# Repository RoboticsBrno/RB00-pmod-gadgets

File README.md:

# pmod-gadgets

Repozitář se všemi rozšířenímí pro desky nejen z [Robotického tábora]("https://robotickytabor.cz")

- [Jak přidat svůj projekt](PMOD.md)

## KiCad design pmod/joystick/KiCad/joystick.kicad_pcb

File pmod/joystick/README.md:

# Joystick PMOD

Tento modul umožňuje připojit joystick k vašemu systému PMOD. Poskytuje jednoduché rozhraní pro čtení polohy páčky a tlačítka.

[Manuál](manual.md){ .md-button .md-button--primary }

|  |  |
| --- | --- |

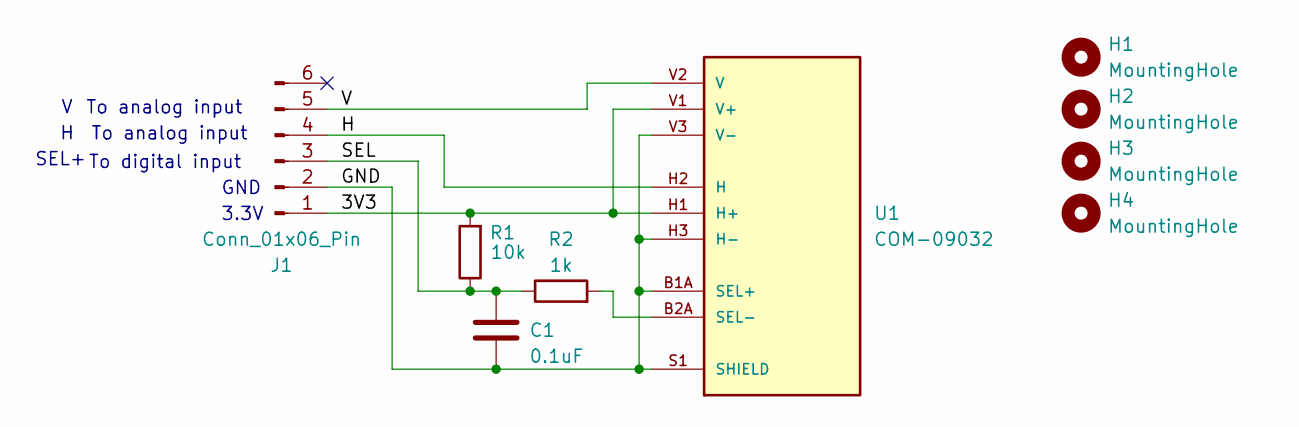
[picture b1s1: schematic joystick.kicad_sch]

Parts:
C1: 0.1uF; C_1206_3216Metric_Pad1.33x1.80mm_HandSolder
H1, H2, H3, H4: MountingHole; MountingHole_3.2mm_M3
J1: Conn_01x06_Pin; PinHeader_1x06_P2.54mm_Horizontal
R1: 10k; R_1206_3216Metric_Pad1.30x1.75mm_HandSolder
R2: 1k; R_1206_3216Metric_Pad1.30x1.75mm_HandSolder
U1: COM-09032; joystick; PARTREV N/A

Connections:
/3V3: J1.1, R1.2, U1.H1 (H+), U1.V1 (V+)
/GND: C1.2, J1.2, U1.B1A (SEL+), U1.H3 (H-), U1.S1 (SHIELD), U1.S2 (SHIELD), U1.S3 (SHIELD), U1.S4 (SHIELD), U1.V3 (V-)
/H: J1.4, U1.H2 (H)
/SEL: C1.1, J1.3, R1.1, R2.1
/V: J1.5, U1.V2 (V)
unnamed: R2.2, U1.B2A (SEL-)

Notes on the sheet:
3.3V
To digital input
To analog input
SEL+
GND

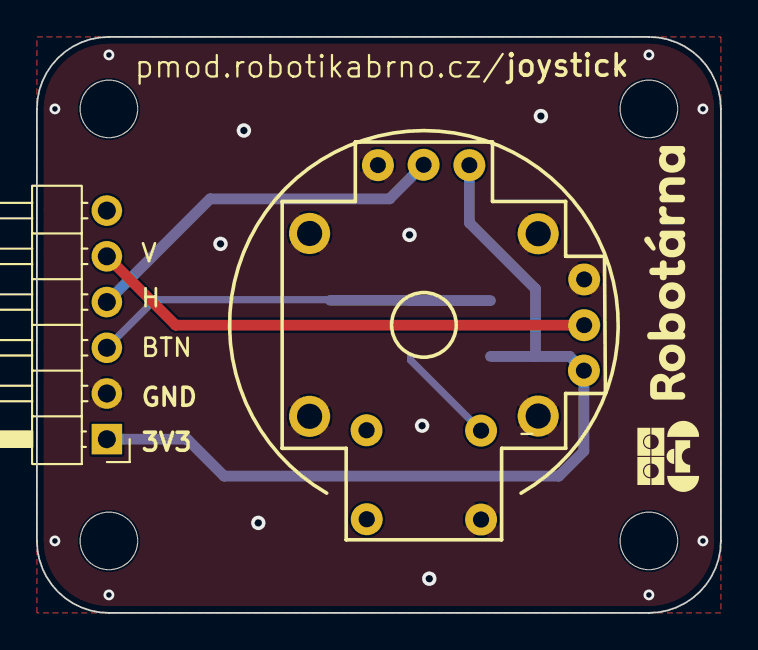
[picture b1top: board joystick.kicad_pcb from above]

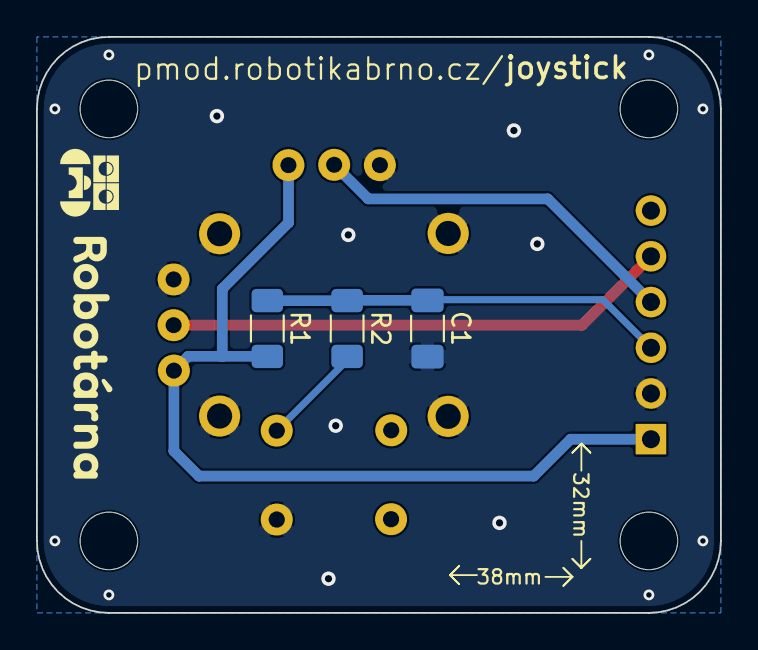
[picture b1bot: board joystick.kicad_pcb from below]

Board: 2 copper layers, 38.0 x 32.0 mm, 9 parts (3 on the bottom side), 6 nets.

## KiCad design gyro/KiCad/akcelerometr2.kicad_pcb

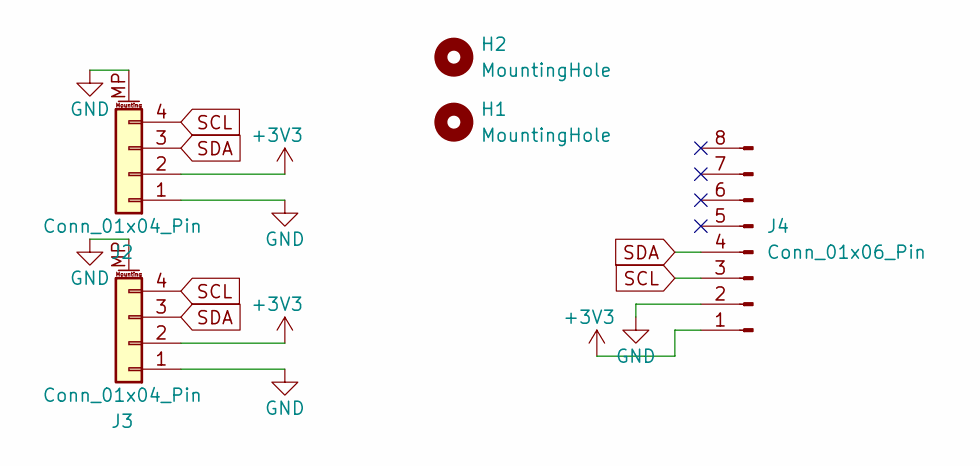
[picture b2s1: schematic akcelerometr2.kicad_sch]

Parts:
H1, H2: MountingHole; MountingHole_3.2mm_M3
J2, J3: Conn_01x04_Pin; JST_SH_SM04B-SRSS-TB_1x04-1MP_P1.00mm_Horizontal; LCSC C160404
J4: Conn_01x06_Pin; PinHeader_1x08_P2.54mm_Vertical

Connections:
+3V3: J2.2, J3.2, J4.1
GND: J2.1, J2.MP (MountPin), J3.1, J3.MP (MountPin), J4.2
SCL: J2.4, J3.4, J4.3
SDA: J2.3, J3.3, J4.4

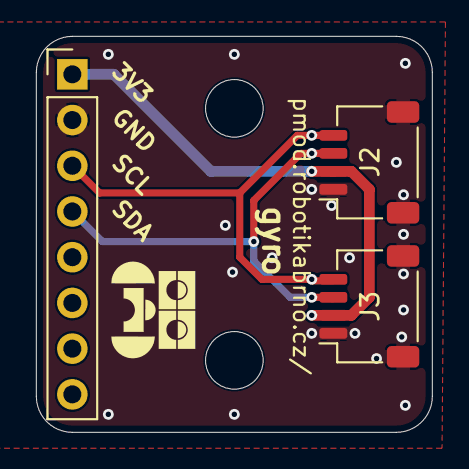
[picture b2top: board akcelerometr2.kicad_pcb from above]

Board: 2 copper layers, 22.0 x 22.0 mm, 5 parts (0 on the bottom side), 4 nets.

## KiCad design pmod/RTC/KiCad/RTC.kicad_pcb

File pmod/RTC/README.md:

# Připojovací modul pro RTC (reálný čas)

Tato deska slouží jako propojovací rozhraní pro snadnou integraci externího RTC modulu (modulu reálného času) do vašeho projektu.

[Manuál](manual.md){ .md-button .md-button--primary }

|  |  |
| --- | --- |

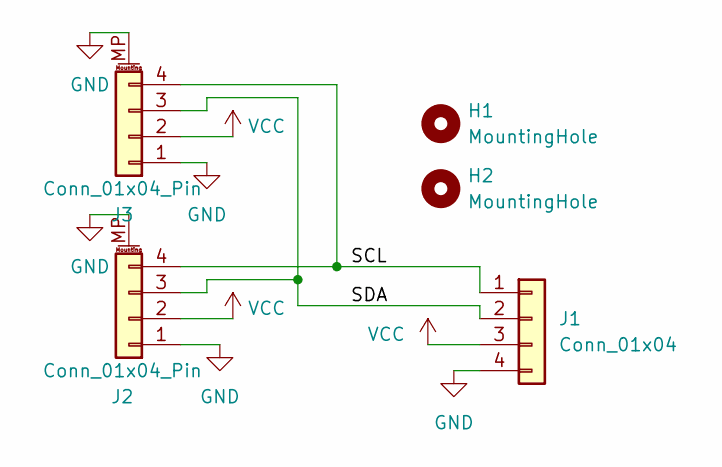
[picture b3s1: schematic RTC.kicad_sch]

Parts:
H1, H2: MountingHole; MountingHole_3.2mm_M3
J1: Conn_01x04; PinHeader_1x04_P2.54mm_Vertical
J2, J3: Conn_01x04_Pin; JST_SH_SM04B-SRSS-TB_1x04-1MP_P1.00mm_Horizontal; LCSC C160404

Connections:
/SCL: J1.1, J2.4, J3.4
/SDA: J1.2, J2.3, J3.3
GND: J1.4, J2.1, J2.MP (MountPin), J3.1, J3.MP (MountPin)
VCC: J1.3, J2.2, J3.2

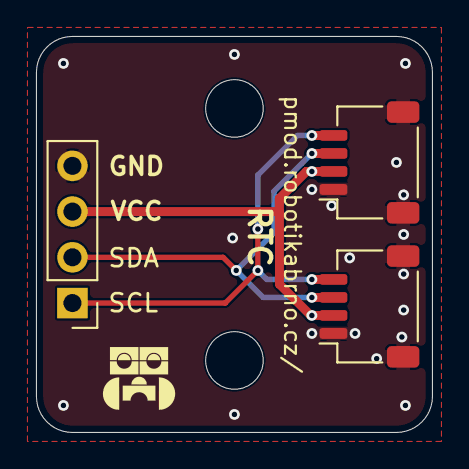
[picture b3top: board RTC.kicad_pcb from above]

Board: 2 copper layers, 22.0 x 22.0 mm, 5 parts (0 on the bottom side), 4 nets.

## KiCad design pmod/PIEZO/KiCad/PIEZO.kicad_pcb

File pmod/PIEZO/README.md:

# Piezoelektrický generátor zvuku

Tento modul slouží k vytváření zvuků pomocí piezoelektrického bzučáku.

[Manuál](manual.md){ .md-button .md-button--primary }

|  |  |
| --- | --- |

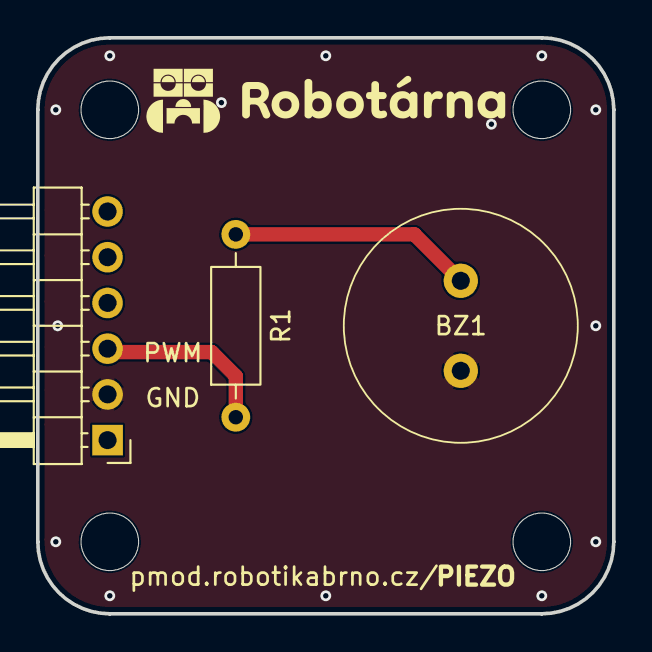
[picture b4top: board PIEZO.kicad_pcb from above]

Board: 2 copper layers, 32.0 x 32.0 mm, 3 parts (0 on the bottom side), 3 nets.

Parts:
BZ1: Buzzer; buzzer
J1: Conn_01x06_Pin; PinHeader_1x06_P2.54mm_Horizontal
R1: 330R; R_Axial_DIN0207_L6.3mm_D2.5mm_P10.16mm_Horizontal

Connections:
GND: BZ1.2 (-), J1.2
unnamed: BZ1.1 (+), R1.2
PWM: J1.3, R1.1

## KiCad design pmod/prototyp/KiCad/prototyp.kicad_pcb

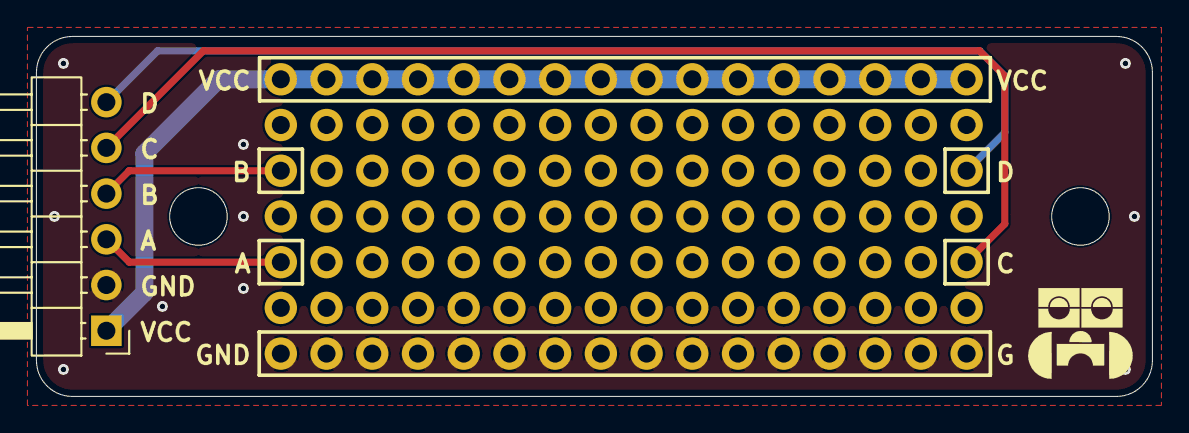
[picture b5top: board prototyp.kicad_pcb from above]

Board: 2 copper layers, 62.0 x 20.0 mm, 115 parts (0 on the bottom side), 6 nets.

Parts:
H1, H2, H3, H4, H5, H6, H7, H8, H9, H10, H11, H12, H13, H14, H15, H16, H17, H18, H19, H20, H21, H22, H23, H24, H25, H26, H27, H28, H29, H30, H31, H32, H33, H34, H35, H36, H37, H38, H39, H40, H41, H42, H43, H44, H45, H46, H47, H48, H49, H50, H51, H52, H53, H54, H55, H56, H57, H58, H59, H60, H61, H62, H63, H64, H65, H66, H67, H68, H69, H70, H71, H72, H73, H74, H75, H76, H77, H78, H79, H80, H81, H82, H83, H84, H85, H86, H87, H88, H89, H90, H91, H92, H93, H94, H95, H96, H97, H98, H99, H100, H101, H102, H103, H104, H105, H106, H107, H108, H109, H110, H111, H112: Hole
H113, H114: MountingHole; MountingHole_3.2mm_M3
J1: Conn_01x06_Pin; PinHeader_1x06_P2.54mm_Horizontal

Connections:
A: H33.1, J1.3
B: H65.1, J1.4
C: H48.1, J1.5
D: H80.1, J1.6
GND: H1.1, H2.1, H3.1, H4.1, H5.1, H6.1, H7.1, H8.1, H9.1, H10.1, H11.1, H12.1, H13.1, H14.1, H15.1, H16.1, J1.2
VCC: H97.1, H98.1, H99.1, H100.1, H101.1, H102.1, H103.1, H104.1, H105.1, H106.1, H107.1, H108.1, H109.1, H110.1, H111.1, H112.1, J1.1

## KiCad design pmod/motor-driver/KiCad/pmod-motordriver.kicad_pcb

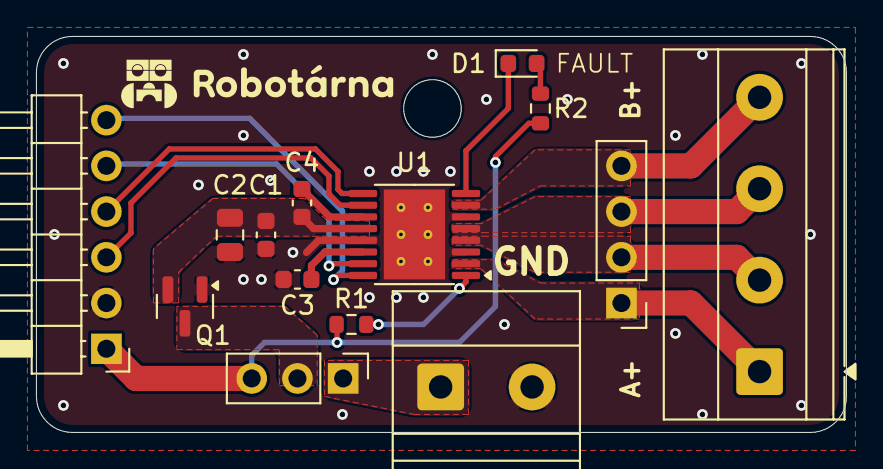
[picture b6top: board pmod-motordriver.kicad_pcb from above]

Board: 2 copper layers, 45.0 x 22.0 mm, 15 parts (0 on the bottom side), 18 nets.

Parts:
C1: 10u; C_0603_1608Metric
C2: 22u; C_0805_2012Metric
C3: 2.2u; C_0603_1608Metric
C4: 100n; C_0603_1608Metric
D1: LED; LED_0603_1608Metric
H1: MountingHole; MountingHole_3.2mm_M3
J1: Conn_01x06_Pin; PinHeader_1x06_P2.54mm_Horizontal
J2: Screw_Terminal_01x02; TerminalBlock_Phoenix_MKDS-1,5-2-5.08_1x02_P5.08mm_Horizont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
J4: Conn_01x04_Pin; PinHeader_1x04_P2.54mm_Vertical
J5: Screw_Terminal_01x04; TerminalBlock_Phoenix_MKDS-1,5-4-5.08_1x04_P5.08mm_Horizont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
JP1: Jumper_3_Bridged12; PinHeader_1x03_P2.54mm_Vertical
Q1: AO3401A; SOT-23
R1: 10k; R_0603_1608Metric
R2: 1k; R_0603_1608Metric
U1: DRV8833PWP; HTSSOP-16-1EP_4.4x5mm_P0.65mm_EP3.4x5mm_Mask2.46x2.31mm_The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

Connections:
+5V: J1.1, JP1.3 (B), R1.1, R2.1
/AOUT1: J4.1, J5.1, U1.2 (AOUT1)
/AOUT2: J4.2, J5.2, U1.4 (AOUT2)
/BOUT1: J4.4, J5.4, U1.7 (BOUT1)
/BOUT2: J4.3, J5.3, U1.5 (BOUT2)
AIN1: J1.6, U1.16 (AIN1)
AIN2: J1.5, U1.15 (AIN2)
BIN1: J1.4, U1.9 (BIN1)
BIN2: J1.3, U1.10 (BIN2)
GND: C1.2, C2.2, C3.2, J1.2, J2.2, Q1.1 (G), U1.3 (AISEN), U1.6 (BISEN), U1.13 (GND), U1.17 (GND)
unnamed: D1.2 (A), R2.2
unnamed: D1.1 (K), U1.8 (~FAULT)
unnamed: J2.1, JP1.1 (A)
unnamed: JP1.2 (C), Q1.3 (D)
unnamed: C4.1, U1.11 (VCP)
unnamed: C3.1, U1.14 (VINT)
unnamed: R1.2, U1.1 (~SLEEP)
VCC: C1.1, C2.1, C4.2, Q1.2 (S), U1.12 (VM)

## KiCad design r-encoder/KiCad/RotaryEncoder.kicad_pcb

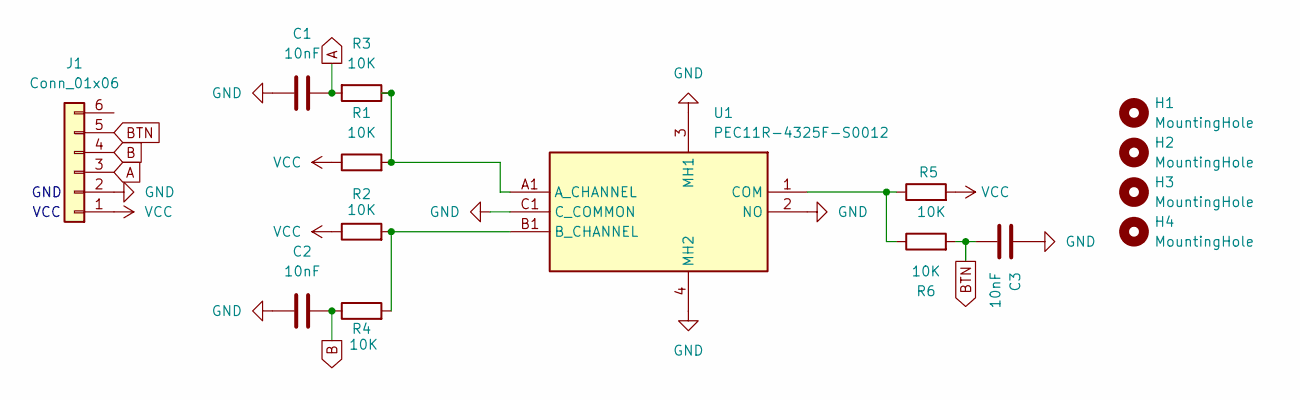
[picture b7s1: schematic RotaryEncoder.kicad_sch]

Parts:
C1, C2, C3: 10nF; C_Disc_D3.8mm_W2.6mm_P2.50mm
H1, H2, H3, H4: MountingHole; MountingHole_3.2mm_M3
J1: Conn_01x06; PinHeader_1x06_P2.54mm_Horizontal
R1, R2, R3, R4, R5, R6: 10K; R_Axial_DIN0204_L3.6mm_D1.6mm_P5.08mm_Horizontal
U1: PEC11R-4325F-S0012; PEC11R4325FS0012; Mouser Part Number 652-PEC11R4325FS0012

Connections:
A: C1.2, J1.3, R3.2
B: C2.2, J1.4, R4.1
BTN: C3.1, J1.5, R6.2
GND: C1.1, C2.1, C3.2, J1.2, U1.2 (NO), U1.3 (MH1), U1.4 (MH2), U1.C1 (C_COMMON)
unnamed: R1.2, R3.1, U1.A1 (A_CHANNEL)
unnamed: R2.2, R4.2, U1.B1 (B_CHANNEL)
unnamed: R5.1, R6.1, U1.1 (COM)
VCC: J1.1, R1.1, R2.1, R5.2

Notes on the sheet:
VCC
GND

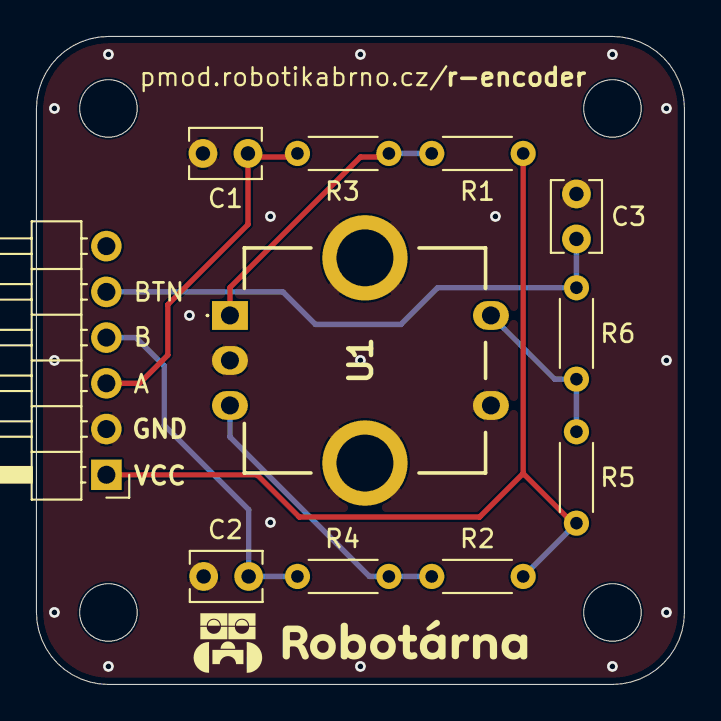
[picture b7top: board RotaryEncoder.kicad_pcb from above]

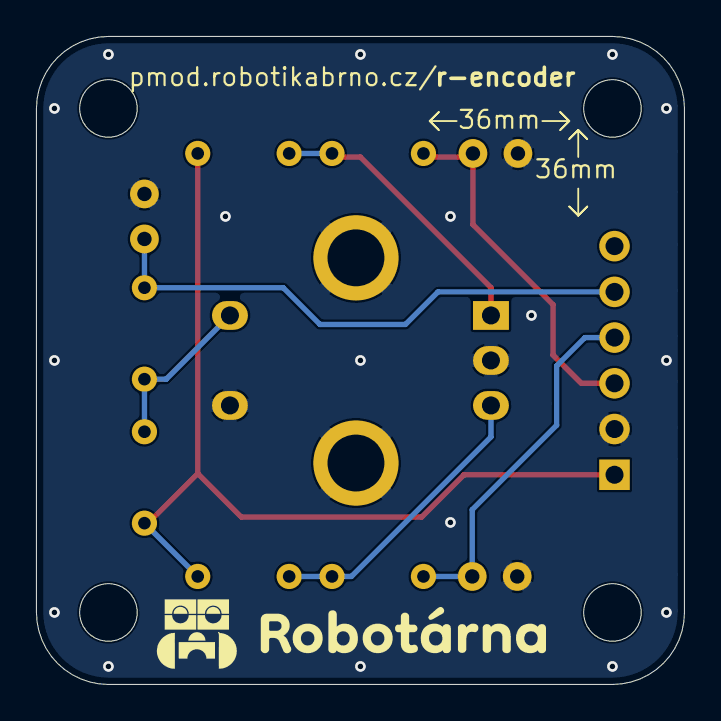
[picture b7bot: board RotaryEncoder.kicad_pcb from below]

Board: 2 copper layers, 36.0 x 36.0 mm, 15 parts (4 on the bottom side), 8 nets.

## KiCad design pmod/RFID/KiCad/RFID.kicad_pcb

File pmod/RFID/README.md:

# RFID Čtečka

Tento modul umožňuje čtení dat z bezkontaktních RFID štítků. 

[Manuál](manual.md){ .md-button .md-button--primary }

|  |  |
| --- | --- |

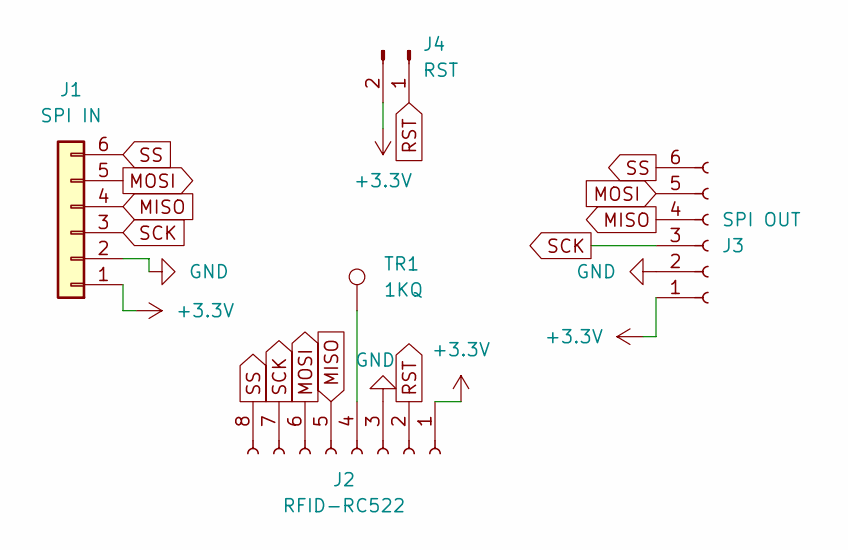
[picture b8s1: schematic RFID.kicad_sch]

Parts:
J1: SPI IN; PinHeader_1x06_P2.54mm_Horizontal
J2: RFID-RC522; PinSocket_1x08_P2.54mm_Vertical
J3: SPI OUT; PinSocket_1x06_P2.54mm_Horizontal
J4: RST; PinHeader_1x02_P2.54mm_Vertical
TR1: 1KQ; SolderWirePad_1x01_SMD_1.5x3mm

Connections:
+3.3V: J1.1, J2.1, J3.1, J4.2
GND: J1.2, J2.3, J3.2
MISO: J1.4, J2.5, J3.4
MOSI: J1.5, J2.6, J3.5
unnamed: J2.4, TR1.1 (1_1)
RST: J2.2, J4.1
SCK: J1.3, J2.7, J3.3
SS: J1.6, J2.8, J3.6

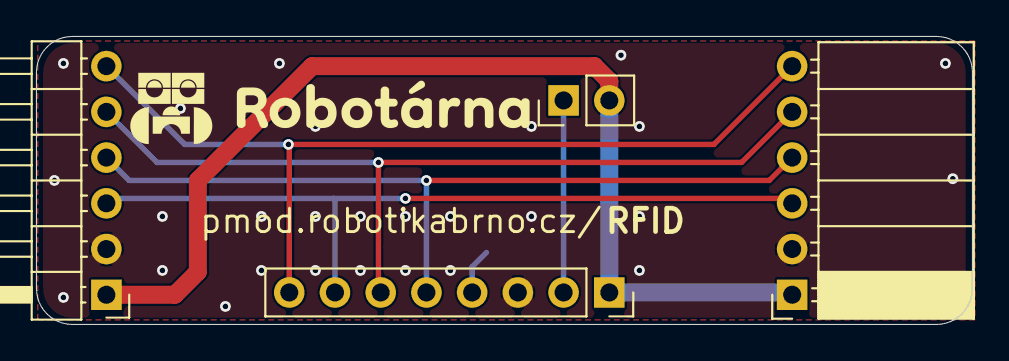
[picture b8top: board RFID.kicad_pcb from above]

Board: 2 copper layers, 52.0 x 16.0 mm, 5 parts (1 on the bottom side), 8 nets.

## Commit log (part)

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2025-10-01 Add base mkdocs
2025-10-01 Add IR module
2025-10-01 Deployed 38c9a23 with MkDocs version: 1.6.0
2025-10-01 Edit CNAME for testing
2025-10-01 Deployed 7b59099 with MkDocs version: 1.6.0
2025-10-12 Add IR KiCad files
2025-10-24 Update IR module
2025-10-28 Update CNAME
2025-11-02 First schematic draft
2025-11-03 docs: more explanation
2025-11-06 Created a new gadget for a DPad. Added navidation entry. Added KiCad project. Added information about gadget.
2025-11-06 Fixed resistor labels to correct format (10K).
2025-11-06 Deployed 896bf81 with MkDocs version: 1.6.0
2025-11-19 docs: update new gadget manual
2025-11-19 Deployed c4c1d63 with MkDocs version: 1.6.0
2025-11-20 board ready for check, need to add version, label...
2025-11-21 feat: add RFID PMOD modul
2025-11-22 add temperature sensor module
2025-11-22 fix temperature: move images to /assets
2025-11-22 Add GitHub Actions workflow for KiCad DRC and export
2025-11-22 Deployed bbfcee4 with MkDocs version: 1.6.0
2025-11-22 Add drc-3d-render.yml workflow file
2025-11-22 Enhance workflow with project filter input
    Added a workflow_dispatch input to filter KiCad projects.
2025-11-22 Enhance DRC and 3D rendering workflow in GitHub Actions
2025-11-22 Deployed c0a35ef with MkDocs version: 1.6.0
2025-11-22 Refactor GitHub Actions workflow for KiCad projects
2025-11-22 Refactor KiCad workflow to separate DRC and 3D render
    Separated the KiCad DRC and 3D render steps into distinct actions.
2025-11-22 Fixed left bottom hole position to be correctly aligned
2025-11-22 Refactor KiCad project detection in workflow
    Updated workflow to find changed KiCad projects and handle project filtering. Enhanced error handling and adjusted job dependencies.
2025-11-22 Deployed a84a255 with MkDocs version: 1.6.0
2025-11-22 Improve change detection in drc-3d-render workflow
    Refactor file change detection logic for improved handling of different GitHub event types and conditions.
2025-11-22 Improve JSON handling and project naming in workflow
    Refactor JSON array creation for changed projects and update workflow names.
2025-11-22 Add full repository check workflow for KiCad
    This workflow performs a full check on all KiCad projects in the repository, including options to generate 3D renders and force checks on all projects.
2025-11-22 Deployed b6c03d1 with MkDocs version: 1.6.0
2025-11-22 Remove strict flag from mkdocs build command
2025-11-23 Basic template copy
2025-11-23 KiCad files from before versioning
2025-11-23 Add dependencies
2025-11-24 Change parts to components
2025-11-24 Remove Analog Devices part
2025-11-24 Replace MAX4466 with LM321U
2025-11-24 Flip P-MOD connector to align with OG PMOD devices and add Mouser hyperlink for the opamp
2025-11-26 pridan bzucak
2025-11-26 pridana dokumentace
2025-11-27 Vytvoření modulu gyro
2025-11-27 Oprava v modulu gyro
2025-11-27 Create KiCad instead of kicad
2025-11-27 Add files via upload
    prosim o kontrolu
2025-11-30 fix2
2025-11-30 Add graphics info
2025-11-30 Deployed 467ebf0 with MkDocs version: 1.6.0
2025-11-30 Update PMOD.md to include folder structure for new PMOD gadgets
2025-11-30 Deployed a60837d with MkDocs version: 1.6.0
2025-11-30 chore: add kicad gitignore
2025-11-30 Deployed c164b2e with MkDocs version: 1.6.0
2025-12-01 Remove circle element from robotarna.svg
    Removed a circle element from the SVG.
2025-12-01 Added labels and logo to board silkscreen
2025-12-01 Work so far done
2025-12-01 work in progress
2025-12-01 Board V2
2025-12-01 ready for merge
2025-12-01 added graphics and protection resistor
2025-12-01 removed Buzzer dir
2025-12-02 Moved silkscreen labels, added dimension labels, added hole size labels
2025-12-02 Added link and logo to front and back. Added hole labels and dimensions
2025-12-02 Added link and logo
2025-12-02 Added hole description and dimensions
2025-12-02 Add fourth hole
2025-12-02 Deployed 72aa7d4 with MkDocs version: 1.6.0
2025-12-02 Hyperlink to board
2025-12-02 Changed R1 R2 an C1 to suit the datasheet of the electret
2025-12-02 rewrote link to match google sheets
2025-12-02 rename Temperature to thermometer to match google sheets
2025-12-02 added drill holes
2025-12-02 Added link to back side
2025-12-02 layer count change + minor fixes
2025-12-02 Shrunk logos to not interfere with pins
2025-12-02 minor changes and fixes
2025-12-02 minor fixes
2025-12-02 Add Mounting hole
2025-12-02 Deployed 8289c9b with MkDocs version: 1.6.0
2025-12-02 add M3 mounting hole
2025-12-02 fix: remove logo from the outside of the board
2025-12-02 Deployed 3317826 with MkDocs version: 1.6.0
2025-12-02 enlarge text and add square logo
2025-12-02 Fixed non connected components, added labels, added logos, added holes
2025-12-02 fix: move KiCad files to correct folders
2025-12-02 Deployed 8c5af15 with MkDocs version: 1.6.0
2025-12-04 Routed board
2025-12-08 fix: small pcb fixes
2025-12-08 fix: rename/move files to correct places
2025-12-08 fix: add copper fill to IR pcb
2025-12-08 fix: connectors
2025-12-08 docs: add all files to mkdocs
2025-12-08 gyro V2
2025-12-08 Deployed 0144617 with MkDocs version: 1.6.0
2025-12-11 add RTC board
2025-12-11 Deployed 769a2f6 with MkDocs version: 1.6.0
2026-01-10 Multiple changes (dzarda):
    odstraněna VBUS dioda
    přidán microUSB
    použit CH340 z Robutka
    USB ESD
    separovány I2C, 2x2 uŠupy
    uŠupy vyvedeny také na pinhead díry
2026-01-15 Round corners and RX TX LEDs
2026-02-13 Added debounce capacitors. Added drill holes for switches.
2026-02-14 Increased track width. Rounded edges of board. Fixed right angle connector.
2026-02-14 Deployed 7db42b7 with MkDocs version: 1.6.0
2026-02-15 modified the pcb to accept better piezo buzzer
2026-02-18 Update IR board - better size, same schematic
2026-02-18 Deployed de0c2bf with MkDocs version: 1.6.0
2026-02-18 pin fix
2026-02-21 text fix
2026-02-24 core_board/Saturn: add review hw version
2026-02-26 added m3 holes and link to README
2026-02-26 core_board/Saturn: update review hw 2nd version
2026-03-04 Created prototype board gadget
2026-03-04 Deployed bea1d0a with MkDocs version: 1.6.0
2026-03-08 Add photoresistor board
2026-03-10 add dual motor driver
2026-03-11 update RTC
    rtc prepracovano na I2C
2026-03-17 Deployed ba208f9 with MkDocs version: 1.6.0
2026-03-17 Deployed 77a73f4 with MkDocs version: 1.6.0
2026-03-17 files moved to proper folder
2026-03-27 better schematic
2026-03-27 Deployed 316a26f with MkDocs version: 1.6.0
2026-03-27 board update
2026-03-27 Deployed d4650ae with MkDocs version: 1.6.0
2026-03-29 minor fixes and mounting hole added
2026-03-29 Deployed d3544d2 with MkDocs version: 1.6.0
2026-03-29 schematic and PCB added
2026-03-29 PCB graphics added
2026-03-29 Deployed 1b09535 with MkDocs version: 1.6.0
2026-03-31 minor error fixes
2026-03-31 Deployed 05c467d with MkDocs version: 1.6.0
2026-03-31 DRC rule fix
2026-03-31 Deployed 1e6e6e1 with MkDocs version: 1.6.0
2026-03-31 bug fix
2026-03-31 Deployed fbf50f4 with MkDocs version: 1.6.0
2026-04-08 update motor driver
2026-04-08 add missing id to motor driver
2026-04-08 add missing silkscreen to motor driver
2026-04-11 polished up PCB of motor driver
2026-04-11 update pictures of motor-driver
2026-04-11 update readme of motor-driver
2026-04-13 replace LED resistor in motor-driver
2026-05-14 fix: Pridal jsem opravy, ktere byly navrzene
2026-05-16 fix: prepare all board for manufacturing
2026-05-16 docs: add images, fix docs
2026-05-17 fix: motor driver board V2
2026-05-17 Deployed d972a79 with MkDocs version: 1.6.0
2026-05-17 fix: comment 3d rendering, currently not working and causes errors and extra CI usage
2026-05-17 Deployed 8c64b74 with MkDocs version: 1.6.0
2026-05-18 docs: fix schema image
2026-05-18 fix: silkscreen tweek
2026-05-18 feat: steps rendering
2026-05-18 fix: better steps rendering
2026-05-19 jine piezo znovu
2026-05-19 fix: correct empty board rendering
2026-05-19 docs: DPad steps
2026-05-19 docs: gyro steps
2026-05-19 docs: IR steps
2026-05-19 docs: joystick steps
2026-05-19 docs: MIC steps
2026-05-19 docs: motor-driver steps
2026-05-19 docs: photoresistor steps
2026-05-19 docs: PIEZO steps
2026-05-19 docs: prototyp steps
2026-05-19 docs: r-encoder steps
2026-05-19 docs: RFID steps
2026-05-19 docs: RTC steps
2026-05-19 docs: thermometer steps
2026-05-19 fix: remove joystick.kicad_prl file
2026-05-19 fix: remove silkscreen for PMOD header
2026-05-19 Deployed a122263 with MkDocs version: 1.6.0
2026-05-19 fix: update PIEZO board
2026-05-19 Deployed 33ea02e with MkDocs version: 1.6.0
2026-05-19 fix: remove kicad_prl files
2026-05-19 Deployed c73d305 with MkDocs version: 1.6.0
2026-05-20 docs: image clipping and automatic highlight generation
2026-05-20 Deployed 8b90671 with MkDocs version: 1.6.0
2026-05-20 docs: automatic schematic generation
2026-05-20 Deployed 8be631c with MkDocs version: 1.6.0
2026-05-20 fix: add back assets folder
2026-05-20 Deployed 02c003b with MkDocs version: 1.6.0
2026-05-20 docs: update PIEZO schematic img link
2026-05-20 Deployed 4f007da with MkDocs version: 1.6.0
2026-05-23 fix: modify RTC board so its the same as gyro board and add LCSC codes
2026-05-23 Deployed 2be6636 with MkDocs version: 1.6.0
2026-05-23 fix: RTC render zoom
2026-05-23 Deployed dbc76a1 with MkDocs version: 1.6.0
2026-05-24 fix: thermometer silkscreen dimensions & voltage
2026-05-24 Deployed efbad4e with MkDocs version: 1.6.0
2026-06-09 fix: remove unnecesary files
2026-06-09 Deployed 6d16b10 with MkDocs version: 1.6.0
2026-06-12 fix: fixed incorrect joystick footprint
2026-06-12 Deployed 15e2d3f with MkDocs version: 1.6.0
2026-06-12 fix: joystick labels
2026-06-12 Deployed 84c3c4d with MkDocs version: 1.6.0
2026-06-14 fix: joystick 3d model
2026-06-14 Deployed 0aec377 with MkDocs version: 1.6.0
2026-06-30 docs: added manuals and READMEs, created manual generation script
2026-06-30 Deployed 4fd4996 with MkDocs version: 1.6.0
